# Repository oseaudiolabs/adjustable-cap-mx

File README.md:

### Adjustable BJT Capacitance Multiplier

Original circuit from http://www.diyaudio.com/forums/solid-state/297921-jumas-easy-peasy-capacitance-multiplier-4.html#post4858155.

### Resources
- [Gerbers](/gerbers)
- [DigiKey BOM](https://www.digikey.com/BOM/Create/CreateSharedBom?bomId=7626991)
- [BOM CSV](/bom.csv)

### Render

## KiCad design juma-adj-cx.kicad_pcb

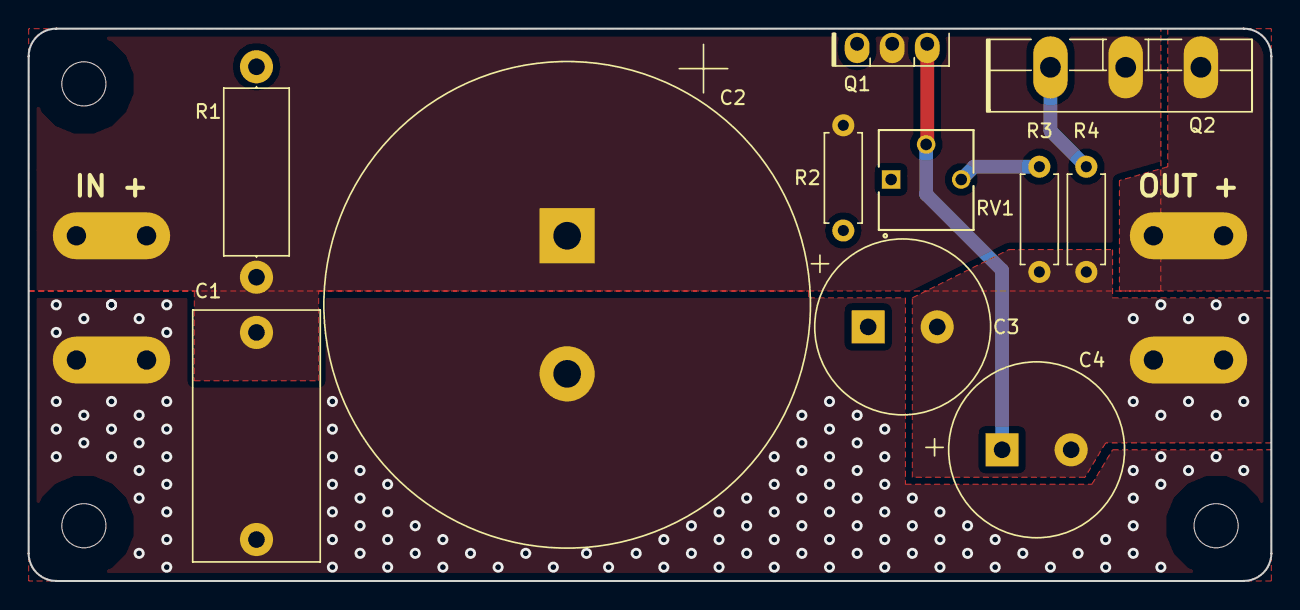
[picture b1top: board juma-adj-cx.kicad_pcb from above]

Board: 2 copper layers, 90.0 x 40.0 mm, 18 parts (0 on the bottom side), 7 nets.

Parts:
C1: 2u; C_Rect_L18.0mm_W9.0mm_P15.00mm_FKS3_FKP3
C2: 22m; CP_Radial_D35.0mm_P10.00mm_SnapIn
C3, C4: 470u; CP_Radial_D12.5mm_P5.00mm
J1: IN+; FASTON_TAB
J2: IN-; FASTON_TAB
J3: OUT+; FASTON_TAB
J4: OUT-; FASTON_TAB
MK1, MK2, MK3: Mounting_Hole; MountingHole_3.2mm_M3_DIN965
Q1: BD139; TO-126-3_Vertical
Q2: 2SC5200; TO-264-3_Vertical
R1: 3k/2W; R_Axial_DIN0414_L11.9mm_D4.5mm_P15.24mm_Horizontal
R2: 150; R_Axial_DIN0207_L6.3mm_D2.5mm_P7.62mm_Horizontal
R3: 10k; R_Axial_DIN0207_L6.3mm_D2.5mm_P7.62mm_Horizontal
R4: 2k; R_Axial_DIN0207_L6.3mm_D2.5mm_P7.62mm_Horizontal
RV1: 2k/.5W; 3362P-1-102LF

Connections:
unnamed: C1.1, C2.1, J1.1, Q1.2, Q2.2, R1.1, R2.1
unnamed: C1.2, C2.2, C3.2, C4.2, J2.1, J4.1, R1.2, R3.2, R4.2
unnamed: C3.1, R2.2, RV1.1
unnamed: C4.1, Q1.3, RV1.2
unnamed: J3.1, Q2.3
unnamed: Q1.1, Q2.1, R4.1
unnamed: R3.1, RV1.3

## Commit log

2018-08-07 initial layout
2018-08-08 separate in/out ground planes
2018-08-09 mark j comment tweak
2018-08-11 v1 for fab

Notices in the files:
parts and their libraries:
Copyright 2016 Accelerated Designs. All rights reserved.
